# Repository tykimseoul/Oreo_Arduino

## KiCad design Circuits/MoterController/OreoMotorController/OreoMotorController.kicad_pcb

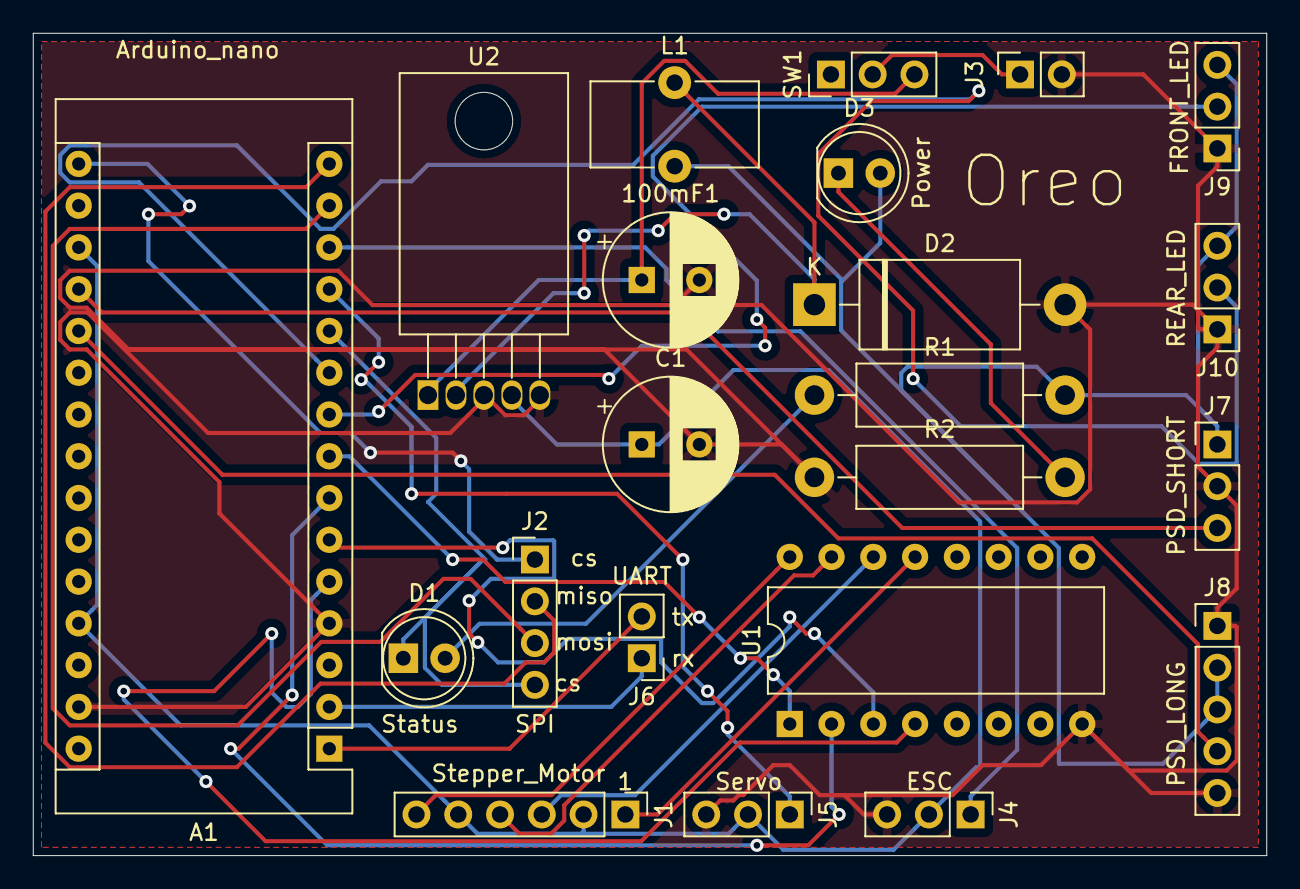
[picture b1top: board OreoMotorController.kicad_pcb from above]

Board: 2 copper layers, 75.0 x 50.0 mm, 22 parts (0 on the bottom side), 26 nets.

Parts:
100mF1: CP; CP_Radial_D8.0mm_P3.50mm
A1: Arduino_Nano_v3.x; Arduino_Nano
C1: CP; CP_Radial_D8.0mm_P3.50mm
D1: STATE_LED; LED_D5.0mm
D2: 1N5822; D_DO-201_P15.24mm_Horizontal
D3: LED; LED_D5.0mm
J1: Conn_01x06_Male; PinHeader_1x06_P2.54mm_Vertical
J2: SPI; PinHeader_1x04_P2.54mm_Vertical
J3: Power; PinSocket_1x02_P2.54mm_Vertical
J4: Conn_01x03_ESC; PinHeader_1x03_P2.54mm_Vertical
J5: Conn_01x03_Servo; PinHeader_1x03_P2.54mm_Vertical
J6: UART; PinHeader_1x02_P2.54mm_Vertical
J7: Conn_1x3_PSD_SHORT; PinHeader_1x03_P2.54mm_Vertical
J8: Conn_01x05_PSD_LONG; PinHeader_1x05_P2.54mm_Vertical
J9, J10: Conn_01x03_Male; PinHeader_1x03_P2.54mm_Vertical
L1: L; L_Toroid_Vertical_L10.0mm_W5.0mm_P5.08mm
R1, R2: 330; R_Axial_DIN0411_L9.9mm_D3.6mm_P15.24mm_Horizontal
SW1: SW_SPDT; PinHeader_1x03_P2.54mm_Vertical
U1: ULN2003; DIP-16_W10.16mm
U2: LM2576HVS-5; TO-220-5_Horizontal_TabDown

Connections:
+5V: A1.18, A1.27, C1.1, D3.2, J1.2, J1.5, J4.2, J5.2, J7.1, J8.2, J8.3, J9.3, J10.3, L1.2, R1.2, U1.9, U2.4
/CS: A1.11, A1.16, D1.1, J2.1, J2.4
/FrontLED: A1.9, J9.2
/MISO: A1.15, J2.2
/MOSI: A1.14, J2.3
/RearLED: A1.10, J10.2
GND: 100mF1.2, A1.4, A1.29, C1.2, D2.2, J3.2, J4.3, J5.3, J7.2, J8.1, J8.5, J9.1, J10.1, R2.1, U1.8, U2.3, U2.5
unnamed: 100mF1.1, SW1.3, U2.1
unnamed: A1.1, J6.2
unnamed: A1.2, J6.1
unnamed: A1.5, U1.4
unnamed: A1.6, U1.3
unnamed: A1.7, U1.2
unnamed: A1.8, U1.1
unnamed: A1.12, J5.1
unnamed: A1.13, J4.1
unnamed: A1.19, J7.3
unnamed: A1.20, J8.4
unnamed: D1.2, R1.1
unnamed: D2.1, L1.1, U2.2
unnamed: D3.1, R2.2
unnamed: J1.1, U1.13
unnamed: J1.3, U1.14
unnamed: J1.4, U1.15
unnamed: J1.6, U1.16
unnamed: J3.1, SW1.2

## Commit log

2019-07-05 ESC motor control
2019-07-06 steering wheel implemented
2019-07-16 add: libraries
2019-07-16 add: lights controller
2019-07-17 add : Circuit
2019-07-17 PCB work done
2019-07-30 add: cmake private
2019-08-06 remove previous files and make new one
2019-08-11 refactor: replace libraries with submodules
2019-08-11 fix: include paths
